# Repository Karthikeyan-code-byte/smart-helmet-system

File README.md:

# smart-helmet-system
Developed an IoT-based Smart Helmet Safety System using ESP32 and sensors to improve road safety through accident detection, emergency alert messaging, and alcohol-based ignition control.

Workflow of Our Project:
  When a crash is detected using the MPU6050, the ESP32 sends a signal to our mobile app via Bluetooth. The app then automatically sends an SMS to the registered emergency contacts, including the GPS location of the accident. Additionally, for safety, when the rider's alcohol level exceeds a predefined threshold, the MQ3 sensor detects it and sends a signal to the ESP32, which turns off the relay. For demonstration, we used an LED to represent the engine-when alcohol levels are high, the LED turns off, indicating that the engine would be disabled.

Novelty of Our Project: The automatic engine cut-off based on alcohol detection enhances rider safety and helps prevent accidents caused by drunk driving.

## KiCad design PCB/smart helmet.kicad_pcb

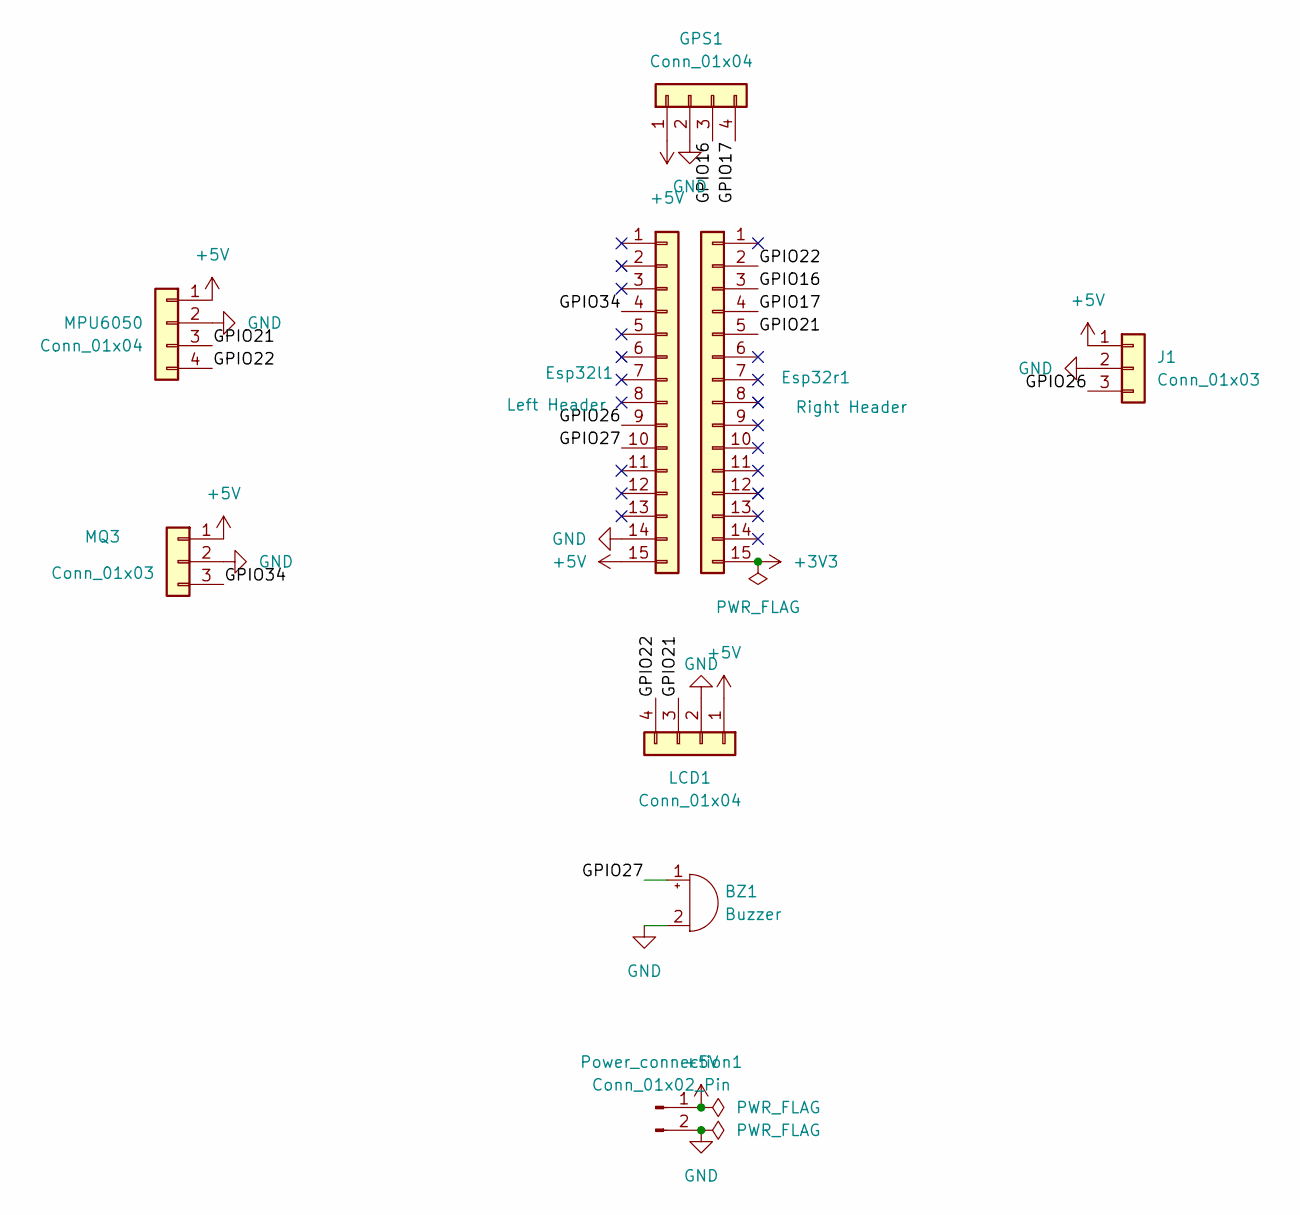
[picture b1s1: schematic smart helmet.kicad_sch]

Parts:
BZ1: Buzzer; Buzzer_12x9.5RM7.6
Esp32l1: Left Header; PinSocket_1x15_P2.54mm_Vertical
Esp32r1: Right Header; PinSocket_1x15_P2.54mm_Vertical
GPS1: Conn_01x04; PinSocket_1x04_P2.54mm_Vertical
J1: Conn_01x03; PinSocket_1x03_P2.54mm_Vertical
LCD1: Conn_01x04; PinSocket_1x04_P2.54mm_Vertical
MPU6050: Conn_01x04; PinSocket_1x04_P2.54mm_Vertical
MQ3: Conn_01x03; PinSocket_1x03_P2.54mm_Vertical
Power_connection1: Conn_01x02_Pin; PinSocket_1x02_P2.54mm_Vertical

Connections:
+3V3: Esp32r1.15
+5V: Esp32l1.15, GPS1.1, J1.1, LCD1.1, MPU6050.1, MQ3.1, Power_connection1.1
/GPIO16: Esp32r1.3, GPS1.3
/GPIO17: Esp32r1.4, GPS1.4
/GPIO21: Esp32r1.5, LCD1.3, MPU6050.3
/GPIO22: Esp32r1.2, LCD1.4, MPU6050.4
/GPIO26: Esp32l1.9, J1.3
/GPIO27: BZ1.1 (+), Esp32l1.10
/GPIO34: Esp32l1.4, MQ3.3
GND: BZ1.2 (-), Esp32l1.14, GPS1.2, J1.2, LCD1.2, MPU6050.2, MQ3.2, Power_connection1.2

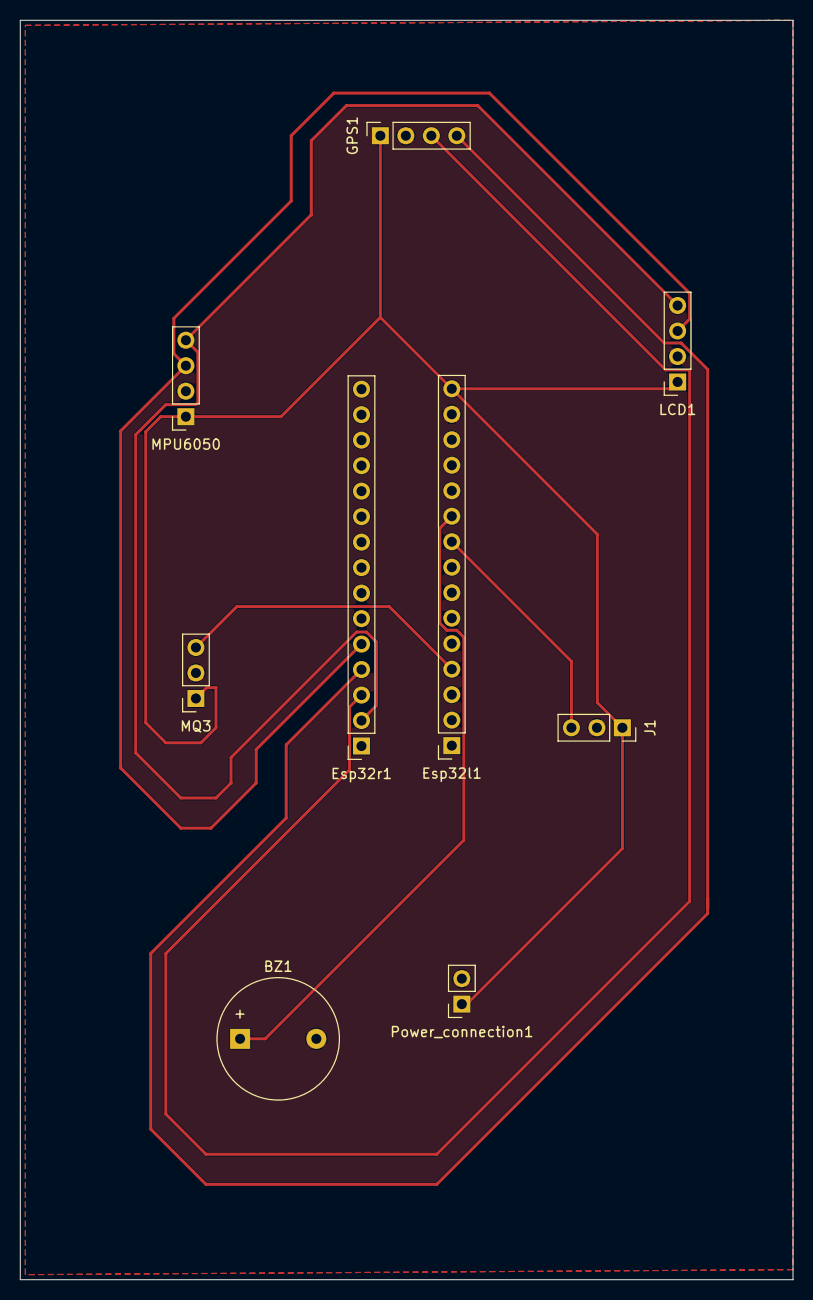
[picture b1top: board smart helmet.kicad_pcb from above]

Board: 2 copper layers, 77.0 x 125.5 mm, 9 parts (0 on the bottom side), 9 nets.

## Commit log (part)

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2026-05-17 Implement accident detection and alcohol monitoring system in helmet
    This code implements an accident detection system using an ESP32. It monitors alcohol levels and accelerometer data to lock the engine and alert the user in case of high alcohol levels or detected ac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
2026-05-17 Enhance README with project workflow and novelty
    Added project workflow and novelty details to README.
2026-05-17 project report
2026-05-17 Circuit diagram of smart helmet system
2026-05-17 Esp32 code
2026-05-17 Create Images
2026-05-17 Project images
2026-05-17 Added prototype images for smart helmet system
